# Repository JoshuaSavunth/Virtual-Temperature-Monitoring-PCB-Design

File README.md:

# Virtual-Temperature-Monitoring-PCB-Design

A computer-based design of a temperature-monitoring PCB using an **STM32G431CBUx** microcontroller.

The project covers the design process from schematic capture and analog signal conditioning through SPICE simulation, PCB layout, firmware development, and manufacturing-file generation.

## Overview

The system models a temperature sensor with a linear output of:

**V<sub>TEMP</sub> = 0.02 × T**

This gives a sensor output of **0 V at 0 °C** and **2.0 V at 100 °C**.

The sensor signal passes through a passive RC low-pass filter before being measured by the STM32 ADC. The calculated temperature is then reported through UART.

### Signal Path

```text
Temperature
     ↓
Virtual Sensor
     ↓
RC Low-Pass Filter
     ↓
STM32 ADC
     ↓
Temperature Calculation
     ↓
UART
     ↓
Host PC
```

### Power Path

```text
5 V Input → AMS1117-3.3 → 3.3 V Rail → STM32 + Supporting Circuitry
```

## PCB Preview

*3D representation of the virtual PCB design.*

## Main Specifications

| Parameter                  | Value         |
| -------------------------- | ------------- |
| MCU                        | STM32G431CBUx |
| Intended temperature range | 0–100 °C      |
| Sensor model               | 0.02 V/°C     |
| Sensor output              | 0–2.0 V       |
| ADC resolution             | 12-bit        |
| ADC reference              | 3.3 V         |
| RC filter                  | 1 kΩ / 100 nF |
| Filter cutoff frequency    | 1.59 kHz      |
| Supply input               | 5 V           |
| Regulated supply           | 3.3 V         |
| UART baud rate             | 115200 bit/s  |

## Hardware Design

The PCB was designed in **KiCad 10** and includes the STM32G431CBUx, analog input filtering, 3.3 V regulation, decoupling, power input, and UART interface.

The RC filter uses:

* **R1 = 1 kΩ**
* **C1 = 100 nF**
* **Cutoff frequency ≈ 1.59 kHz**

The 3.3 V supply is generated from the nominal 5 V input using an **AMS1117-3.3** linear regulator.

### Schematic

*KiCad schematic showing the temperature-sensing, filtering, power, MCU, and UART sections.*

### PCB Layout

*PCB layout showing component placement, routing, and ground copper.*

## Firmware

The STM32 firmware was developed in **C** using **STM32CubeIDE** and the **STM32 Hardware Abstraction Layer (HAL)**.

The firmware configures:

* ADC1 on **PA0 (ADC1_IN1)**
* 12-bit, single-ended ADC conversion
* USART1 TX on **PA9**
* USART1 RX on **PA10**
* UART at **115200 bit/s**

The ADC reading is converted to voltage using the 3.3 V reference and then converted to temperature using the sensor model.

Example UART output:

```text
ADC: 1241, Voltage: 1.000 V, Temperature: 50.00 C
```

The theoretical ADC range extends to approximately 3.3 V. With the sensor model of 0.02 V/°C, this corresponds to a theoretical maximum of **165 °C**, although the intended operating range is **0–100 °C**.

### Firmware Flow

## Simulation and Analysis

SPICE transient simulation was used to examine the behaviour of the RC filter.

The simulated filtered signal showed the expected low-pass behaviour, smoothly approaching the applied sensor voltage following a step change.

The ideal 12-bit ADC resolution is:

```text
3.3 V / 4096 ≈ 0.806 mV/count
```
Some expected values are:

| Temperature | Sensor Voltage | Approx. ADC Code |
| ----------: | -------------: | ---------------: |
|        0 °C |          0.0 V |                0 |
|       25 °C |          0.5 V |              620 |
|       50 °C |          1.0 V |             1241 |
|       75 °C |          1.5 V |             1861 |
|      100 °C |          2.0 V |             2482 |

### SPICE Simulation

*Simulated transient response of the RC low-pass filter at 2.0V.*

## Verification

The project was verified using computer-based design and simulation tools.

Completed checks include:

* KiCad schematic and ERC verification
* SPICE transient simulation
* ADC resolution calculations
* PCB layout and 3D inspection
* Manufacturing-file generation
* STM32 firmware compilation

The final STM32 Debug build completed with:

```text
0 errors
0 warnings
```

The build also generated the firmware output files required for future programming of the microcontroller.

## Lessons Learned

This project provided hands-on experience with:

* Full PCB design workflow (schematic → layout → simulation → manufacturing outputs)
* RC filter analysis (time constant, cutoff frequency, transient response)
* ADC resolution and quantization analysis
* Power regulation and MCU decoupling strategies
* STM32 firmware development (ADC configuration, UART communication)
* Professional documentation and version control practices

## Future Work

The next stage of the project would be to:

1. Fabricate the PCB.
2. Assemble the components.
3. Program the STM32 with the completed firmware.
4. Test the ADC using known input voltages.
5. Verify temperature conversion and UART output.
6. Compare measured results with the theoretical and simulated results.

## Repository Structure

```text
.
├── Firmware/
│   └── STM32CubeIDE project
│
├── KiCad/
│   ├── Schematic
│   ├── PCB layout
│   └── Project files
│
├── Simulation/
│   └── SPICE files
│
├── Manufacturing/
│   ├── Gerbers
│   ├── Drill files
│   └── BOM
│
├── Project Report
│   
│
├── Images/
│   ├── pcb-3d.png
│   ├── schematic.png
│   ├── pcb-layout.png
│   └── spice-response.png
│
└── README.md
```

## Tools

* **KiCad 10** — schematic capture and PCB design
* **STM32CubeIDE** — firmware development
* **SPICE** — analog simulation
* **Git / GitHub** — project version control

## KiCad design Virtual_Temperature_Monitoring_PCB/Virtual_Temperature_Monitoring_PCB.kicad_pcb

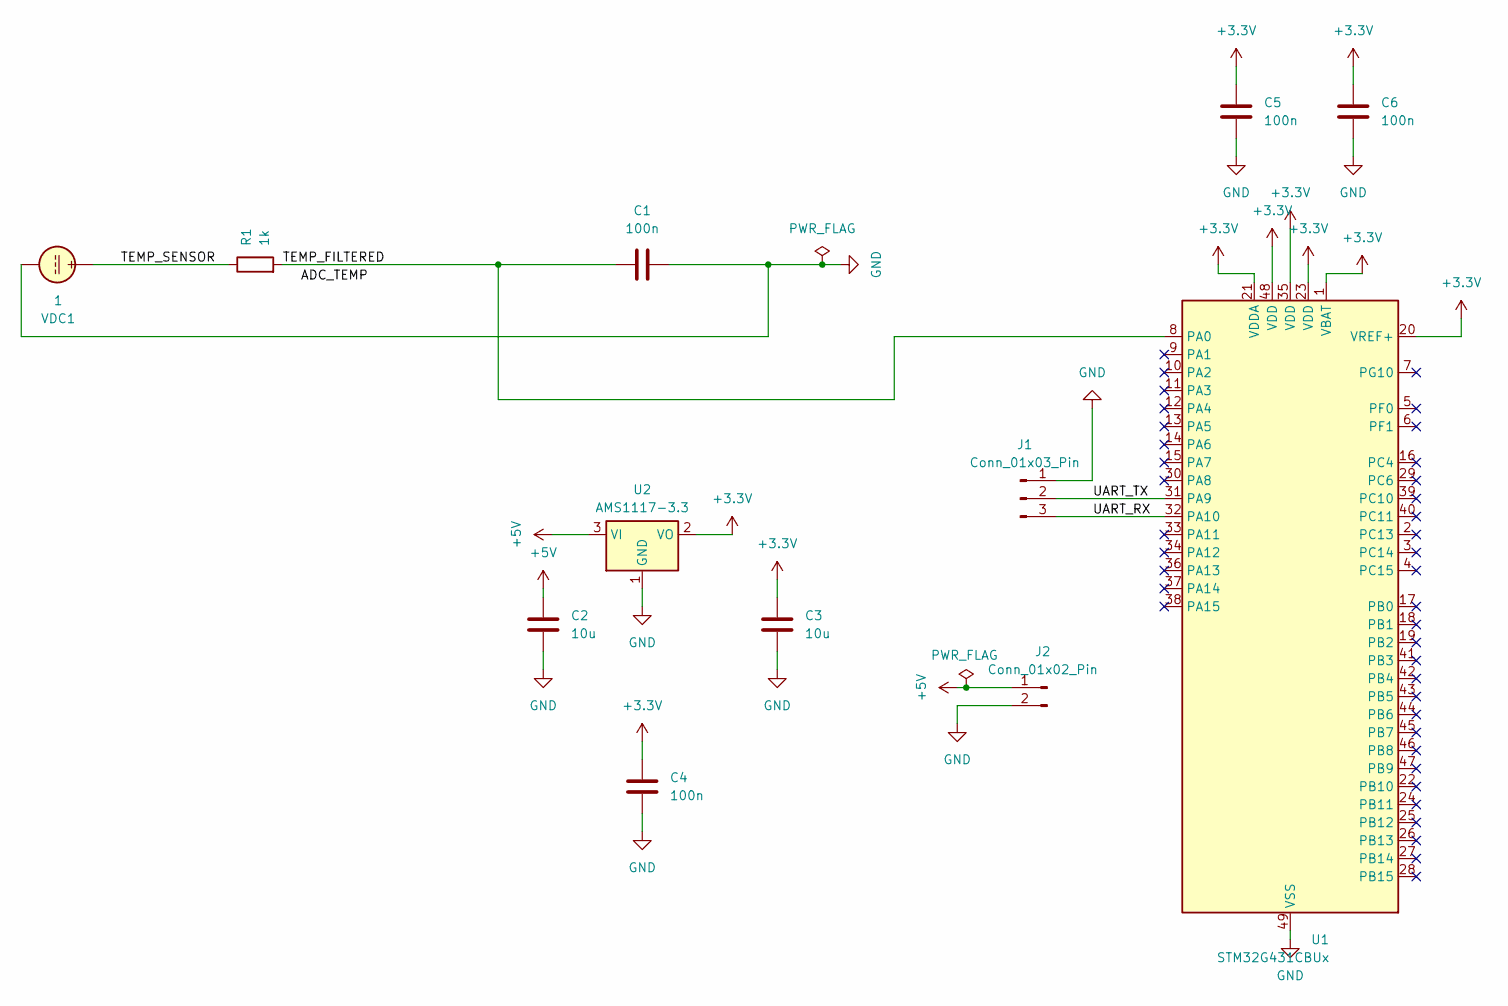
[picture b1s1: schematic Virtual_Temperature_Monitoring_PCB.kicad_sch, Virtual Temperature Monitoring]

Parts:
C1, C4, C5, C6: 100n; C_0603_1608Metric
C2, C3: 10u; C_0805_2012Metric
J1: Conn_01x03_Pin; PinHeader_1x03_P2.54mm_Vertical
J2: Conn_01x02_Pin; PinHeader_1x02_P2.54mm_Vertical
R1: 1k; R_0603_1608Metric
U1: STM32G431CBUx; QFN-48-1EP_7x7mm_P0.5mm_EP5.6x5.6mm
U2: AMS1117-3.3; SOT-223-3_TabPin2
VDC1: 1

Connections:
+3.3V: C3.1, C4.1, C5.1, C6.1, U1.1 (VBAT), U1.20 (VREF+), U1.21 (VDDA), U1.23 (VDD), U1.35 (VDD), U1.48 (VDD), U2.2 (VO)
+5V: C2.1, J2.1, U2.3 (VI)
/TEMP_FILTERED: C1.1, R1.2, U1.8 (PA0)
/TEMP_SENSOR: R1.1, VDC1.1
/UART_RX: J1.3, U1.32 (PA10)
/UART_TX: J1.2, U1.31 (PA9)
GND: C1.2, C2.2, C3.2, C4.2, C5.2, C6.2, J1.1, J2.2, U1.49 (VSS), U2.1 (GND), VDC1.2

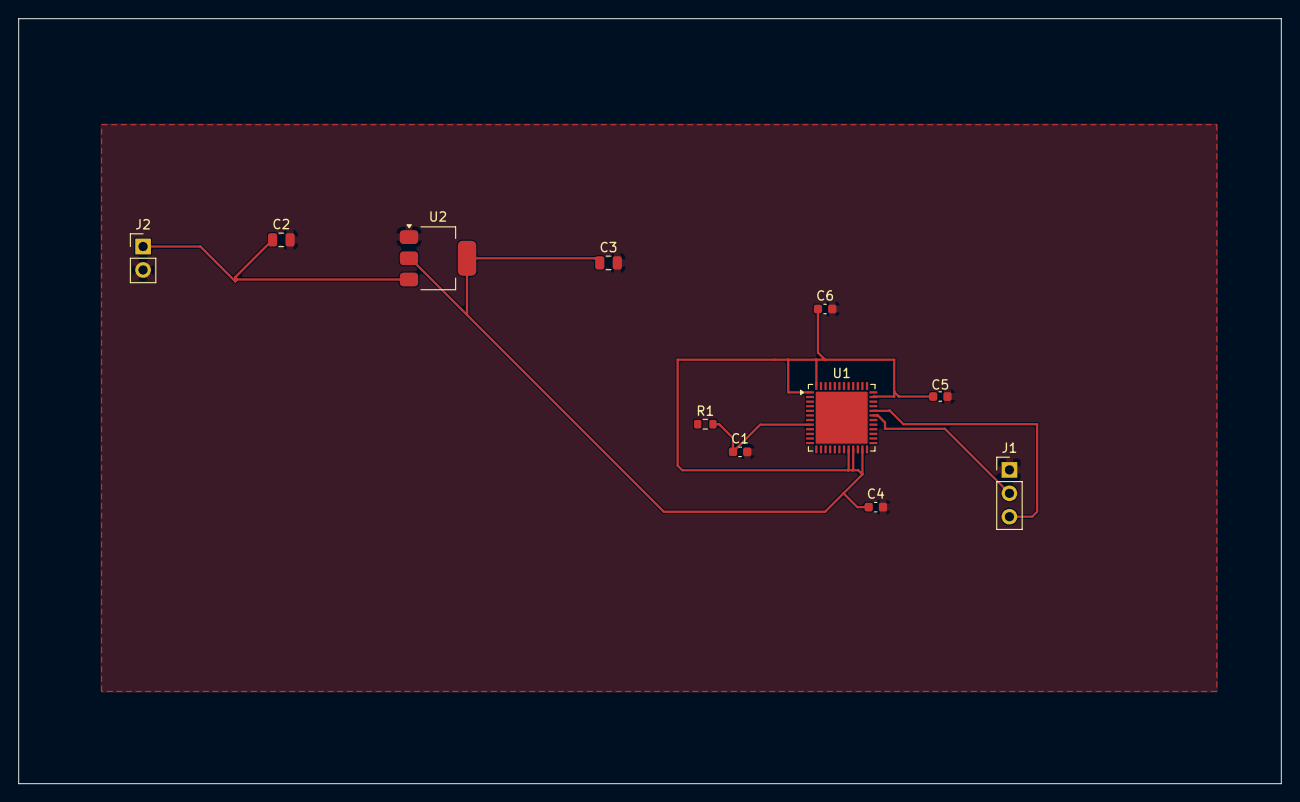
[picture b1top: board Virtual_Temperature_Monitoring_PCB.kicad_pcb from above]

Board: 2 copper layers, 137.0 x 83.0 mm, 11 parts (0 on the bottom side), 6 nets.

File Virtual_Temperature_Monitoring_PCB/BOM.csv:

"Reference","Qty","Value","DNP","Exclude from BOM","Exclude from Board","Exclude from Simulation","Exclude from Position Files","Footprint","Datasheet"
"C1,C4,C5,C6","4","100n","","","","","${EXCLUDE_FROM_POS_FILES}","Capacitor_SMD:C_0603_1608Metric",""
"C2,C3","2","10u","","","","","${EXCLUDE_FROM_POS_FILES}","Capacitor_SMD:C_0805_2012Metric",""
"J1","1","Conn_01x03_Pin","","","","Excluded from simulation","${EXCLUDE_FROM_POS_FILES}","Connector_PinHeader_2.54mm:PinHeader_1x03_P2.54mm_Vertical",""
"J2","1","Conn_01x02_Pin","","","","Excluded from simulation","${EXCLUDE_FROM_POS_FILES}","Connector_PinHeader_2.54mm:PinHeader_1x02_P2.54mm_Vertical",""
"R1","1","1k","","","","","${EXCLUDE_FROM_POS_FILES}","Resistor_SMD:R_0603_1608Metric",""
"U1","1","STM32G431CBUx","","","","Excluded from simulation","${EXCLUDE_FROM_POS_FILES}","Package_DFN_QFN:QFN-48-1EP_7x7mm_P0.5mm_EP5.6x5.6mm","https://www.st.com/resource/en/datasheet/stm32g431cb.pdf"
"U2","1","AMS1117-3.3","","","","Excluded from simulation","${EXCLUDE_FROM_POS_FILES}","Package_TO_SOT_SMD:SOT-223-3_TabPin2","http://www.advanced-monolithic.com/pdf/ds1117.pdf"
"VDC1","1","1","","","Excluded from board","","${EXCLUDE_FROM_POS_FILES}","","https://ngspice.sourceforge.io/docs/ngspice-html-manual/manu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"
